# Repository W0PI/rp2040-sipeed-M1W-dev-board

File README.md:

# rp2040-sipeed-M1W-dev-board

*the names of the PCB files are different cause at the very start i sightly chnaged what i was doing and didnt know how to change kicad project names*

a rp2040 and a sippeed M1W on one board both connected by uart the M1W has a camera and lcd connector aswell as 8 mics in a circle for directional detection

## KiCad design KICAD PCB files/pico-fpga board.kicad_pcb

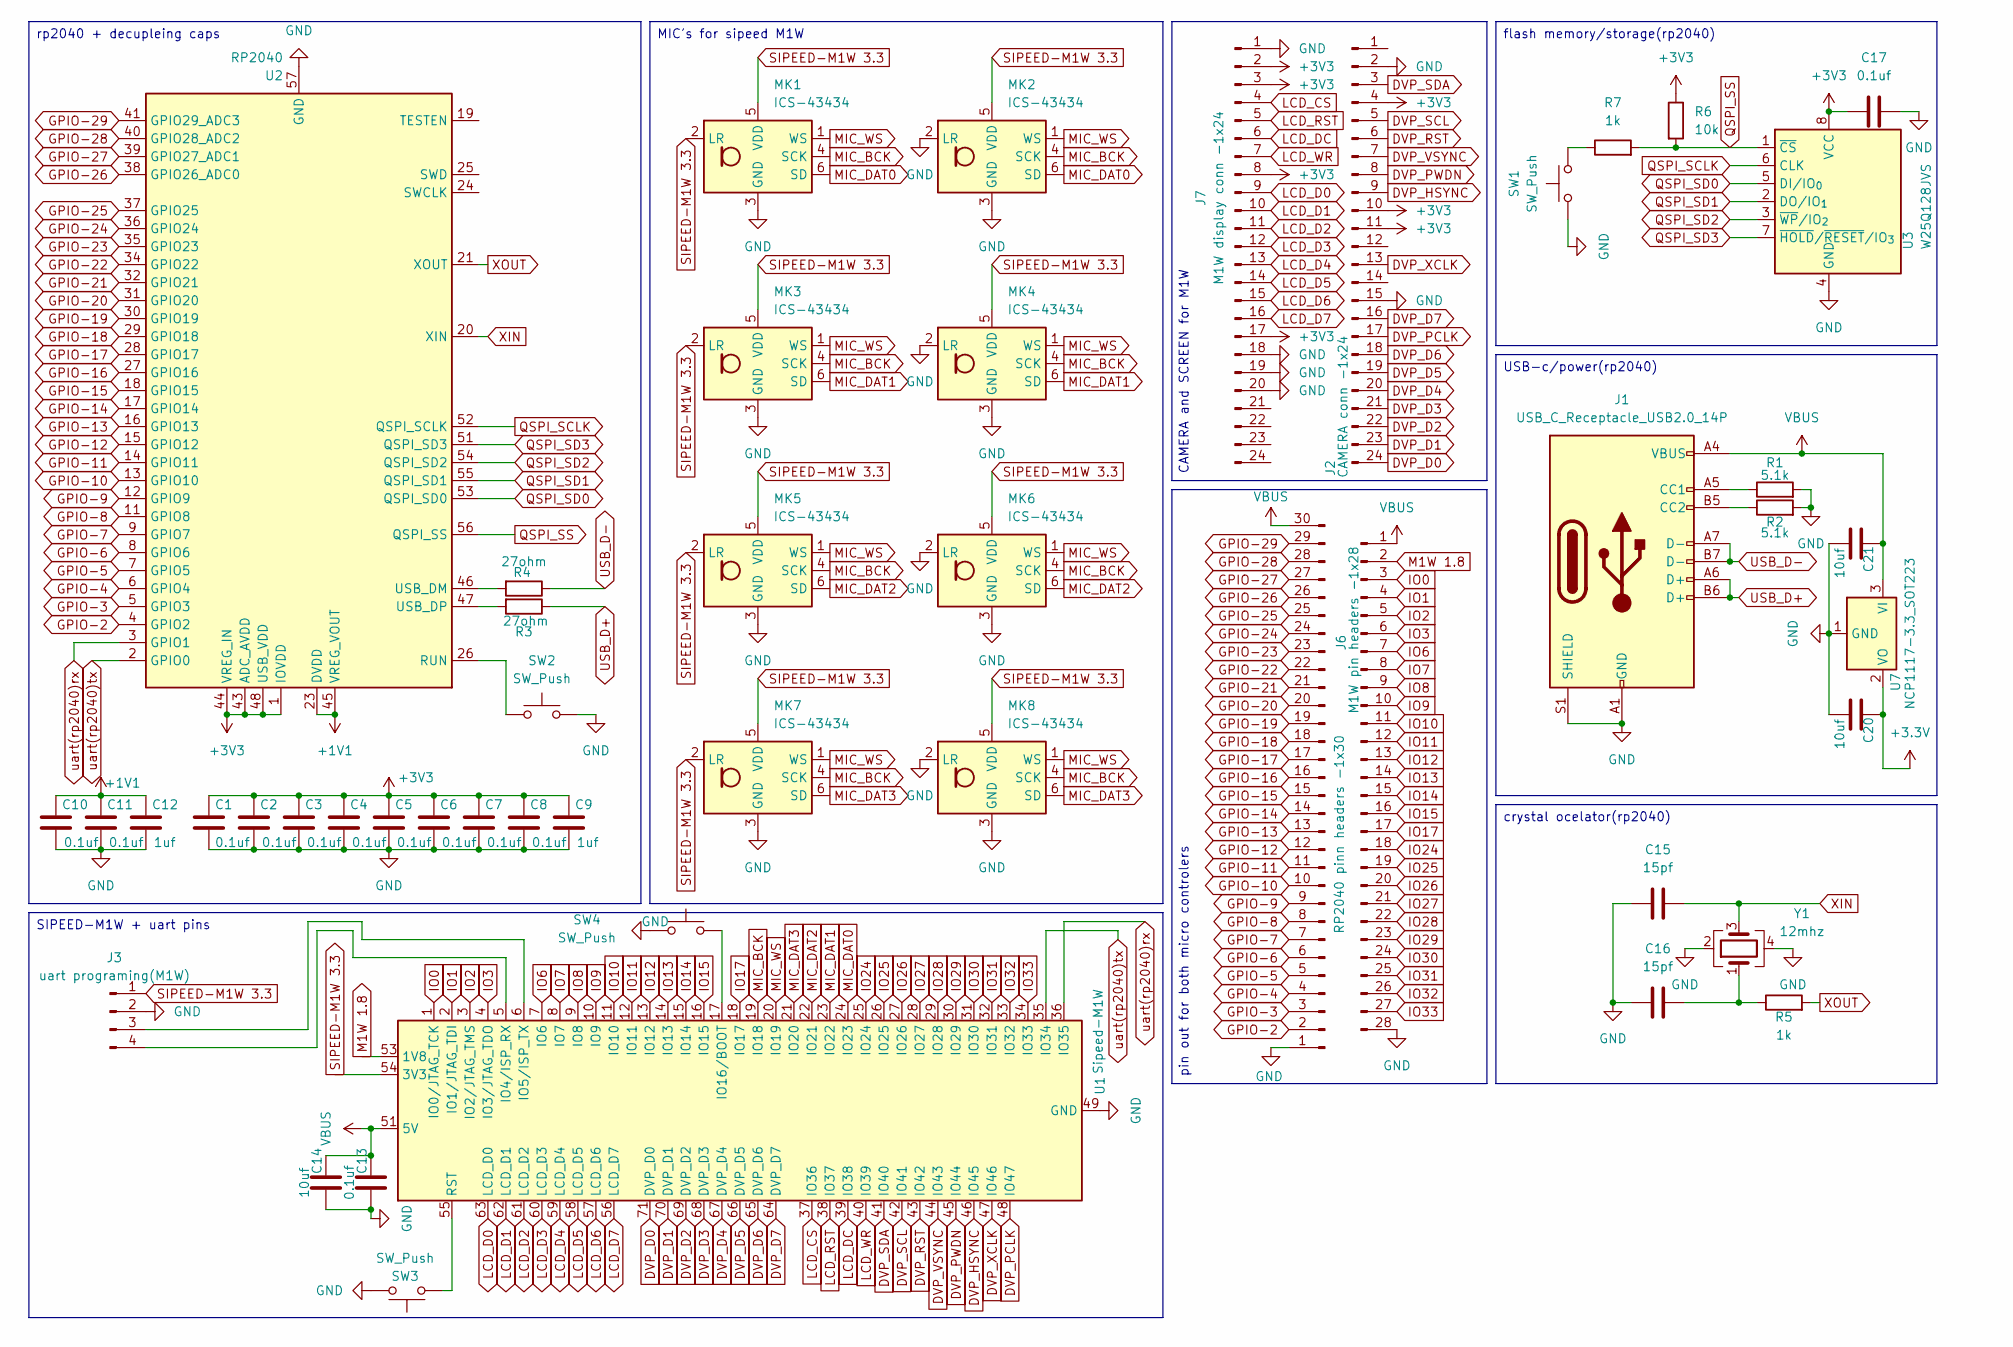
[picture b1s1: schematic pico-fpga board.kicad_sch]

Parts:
C1, C2, C3, C4, C5, C6, C7, C8, C10, C11, C13, C17: 0.1uf; 0805
C9, C12: 1uf; 0805
C14, C20, C21: 10uf; 0805
C15, C16: 15pf; 0805
J1: USB_C_Receptacle_USB2.0_14P; USB-C
J2: CAMERA conn -1x24; CAMERA conn
J3: uart programing(M1W); PinHeader_1x04_P2.54mm_Horizontal
J4: RP2040 pinn headers -1x30; PinHeader_1x30_P2.54mm_Vertical
J6: M1W pin headers -1x28; PinHeader_1x28_P2.54mm_Vertical
J7: M1W display conn -1x24; CAMERA conn
MK1, MK2, MK3, MK4, MK5, MK6, MK7, MK8: ICS-43434; InvenSense_ICS-43434-6_3.5x2.65mm
R1, R2: 5.1k; 0805
R3, R4: 27ohm; 0805
R5, R7: 1k; 0805
R6: 10k; 0805
SW1, SW2, SW3, SW4: SW_Push; button
U1: Sipeed-M1W
U2: RP2040; QFN-56-1EP_7x7mm_P0.4mm_EP3.2x3.2mm
U3: W25Q128JVS; SOIC-8_5.3x5.3mm_P1.27mm
U7: NCP1117-3.3_SOT223; SOT-223-3_TabPin2
Y1: 12mhz; 12mhz crystal

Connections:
+1V1: C10.1, C11.1, C12.1, U2.23 (DVDD), U2.45 (VREG_VOUT), U2.50 (DVDD)
+3.3V: C20.1, U7.2 (VO)
+3V3: C1.1, C2.1, C3.1, C4.1, C5.1, C6.1, C7.1, C8.1, C9.1, C17.1, J2.4, J2.10, J2.11, J7.2, J7.3, J7.8, J7.17, R6.1, U2.1 (IOVDD), U2.10 (IOVDD), U2.22 (IOVDD), U2.33 (IOVDD), U2.42 (IOVDD), U2.43 (ADC_AVDD), U2.44 (VREG_IN), U2.48 (USB_VDD), U2.49 (IOVDD), U3.8 (VCC)
DVP_D0: J2.24, U1.71 (DVP_D0)
DVP_D1: J2.23, U1.70 (DVP_D1)
DVP_D2: J2.22, U1.69 (DVP_D2)
DVP_D3: J2.21, U1.68 (DVP_D3)
DVP_D4: J2.20, U1.67 (DVP_D4)
DVP_D5: J2.19, U1.66 (DVP_D5)
DVP_D6: J2.18, U1.65 (DVP_D6)
DVP_D7: J2.16, U1.64 (DVP_D7)
DVP_HSYNC: J2.9, U1.46 (IO45)
DVP_PCLK: J2.17, U1.48 (IO47)
DVP_PWDN: J2.8, U1.45 (IO44)
DVP_RST: J2.6, U1.43 (IO42)
DVP_SCL: J2.5, U1.42 (IO41)
DVP_SDA: J2.3, U1.41 (IO40)
DVP_VSYNC: J2.7, U1.44 (IO43)
DVP_XCLK: J2.13, U1.47 (IO46)
GND: C1.2, C2.2, C3.2, C4.2, C5.2, C6.2, C7.2, C8.2, C9.2, C10.2, C11.2, C12.2, C13.1, C14.1, C15.1, C16.1, C17.2, C20.2, C21.2, J1.A1 (GND), J1.A12 (GND), J1.B1 (GND), J1.B12 (GND), J1.S1 (SHIELD), J2.2, J2.15, J3.2, J4.1, J6.28, J7.1, J7.18, J7.19, J7.20, MK1.3 (GND), MK2.2 (LR), MK2.3 (GND), MK3.3 (GND), MK4.2 (LR), MK4.3 (GND), MK5.3 (GND), MK6.2 (LR), MK6.3 (GND), MK7.3 (GND), MK8.2 (LR), MK8.3 (GND), R1.2, R2.2, SW1.1, SW2.2, SW3.2, SW4.1, U1.49 (GND), U1.50 (GND), U1.72 (GND), U2.57 (GND), U3.4 (GND), U7.1 (GND), Y1.2, Y1.4
GPIO-2: J4.2, U2.4 (GPIO2)
GPIO-3: J4.3, U2.5 (GPIO3)
GPIO-4: J4.4, U2.6 (GPIO4)
GPIO-5: J4.5, U2.7 (GPIO5)
GPIO-6: J4.6, U2.8 (GPIO6)
GPIO-7: J4.7, U2.9 (GPIO7)
GPIO-8: J4.8, U2.11 (GPIO8)
GPIO-9: J4.9, U2.12 (GPIO9)
GPIO-10: J4.10, U2.13 (GPIO10)
GPIO-11: J4.11, U2.14 (GPIO11)
GPIO-12: J4.12, U2.15 (GPIO12)
GPIO-13: J4.13, U2.16 (GPIO13)
GPIO-14: J4.14, U2.17 (GPIO14)
GPIO-15: J4.15, U2.18 (GPIO15)
GPIO-16: J4.16, U2.27 (GPIO16)
GPIO-17: J4.17, U2.28 (GPIO17)
GPIO-18: J4.18, U2.29 (GPIO18)
GPIO-19: J4.19, U2.30 (GPIO19)
GPIO-20: J4.20, U2.31 (GPIO20)
GPIO-21: J4.21, U2.32 (GPIO21)
GPIO-22: J4.22, U2.34 (GPIO22)
GPIO-23: J4.23, U2.35 (GPIO23)
GPIO-24: J4.24, U2.36 (GPIO24)
GPIO-25: J4.25, U2.37 (GPIO25)
GPIO-26: J4.26, U2.38 (GPIO26_ADC0)
GPIO-27: J4.27, U2.39 (GPIO27_ADC1)
GPIO-28: J4.28, U2.40 (GPIO28_ADC2)
GPIO-29: J4.29, U2.41 (GPIO29_ADC3)
IO0: J6.3, U1.1 (IO0/JTAG_TCK)
IO1: J6.4, U1.2 (IO1/JTAG_TDI)
IO2: J6.5, U1.3 (IO2/JTAG_TMS)
IO3: J6.6, U1.4 (IO3/JTAG_TDO)
IO6: J6.7, U1.7 (IO6)
IO7: J6.8, U1.8 (IO7)
IO8: J6.9, U1.9 (IO8)
IO9: J6.10, U1.10 (IO9)
IO10: J6.11, U1.11 (IO10)
IO11: J6.12, U1.12 (IO11)
IO12: J6.13, U1.13 (IO12)
IO13: J6.14, U1.14 (IO13)
IO14: J6.15, U1.15 (IO14)
IO15: J6.16, U1.16 (IO15)
IO17: J6.17, U1.18 (IO17)
IO24: J6.18, U1.25 (IO24)
IO25: J6.19, U1.26 (IO25)
IO26: J6.20, U1.27 (IO26)
IO27: J6.21, U1.28 (IO27)
IO28: J6.22, U1.29 (IO28)
IO29: J6.23, U1.30 (IO29)
IO30: J6.24, U1.31 (IO30)
IO31: J6.25, U1.32 (IO31)
IO32: J6.26, U1.33 (IO32)
IO33: J6.27, U1.34 (IO33)
LCD_CS: J7.4, U1.37 (IO36)
LCD_D0: J7.9, U1.63 (LCD_D0)
LCD_D1: J7.10, U1.62 (LCD_D1)
LCD_D2: J7.11, U1.61 (LCD_D2)
LCD_D3: J7.12, U1.60 (LCD_D3)
LCD_D4: J7.13, U1.59 (LCD_D4)
LCD_D5: J7.14, U1.58 (LCD_D5)
LCD_D6: J7.15, U1.57 (LCD_D6)
LCD_D7: J7.16, U1.56 (LCD_D7)
LCD_DC: J7.6, U1.39 (IO38)
LCD_RST: J7.5, U1.38 (IO37)
LCD_WR: J7.7, U1.40 (IO39)
M1W 1.8: J6.2, U1.53 (1V8)
MIC_BCK: MK1.4 (SCK), MK2.4 (SCK), MK3.4 (SCK), MK4.4 (SCK), MK5.4 (SCK), MK6.4 (SCK), MK7.4 (SCK), MK8.4 (SCK), U1.19 (IO18)
MIC_DAT0: MK1.6 (SD), MK2.6 (SD), U1.24 (IO23)
MIC_DAT1: MK3.6 (SD), MK4.6 (SD), U1.23 (IO22)
MIC_DAT2: MK5.6 (SD), MK6.6 (SD), U1.22 (IO21)
MIC_DAT3: MK7.6 (SD), MK8.6 (SD), U1.21 (IO20)
MIC_WS: MK1.1 (WS), MK2.1 (WS), MK3.1 (WS), MK4.1 (WS), MK5.1 (WS), MK6.1 (WS), MK7.1 (WS), MK8.1 (WS), U1.20 (IO19)
unnamed: C16.2, R5.1, Y1.1
unnamed: J1.A5 (CC1), R1.1
unnamed: J1.B5 (CC2), R2.1
unnamed: J3.3, U1.6 (IO5/ISP_TX)
unnamed: J3.4, U1.5 (IO4/ISP_RX)
unnamed: R7.1, SW1.2
unnamed: SW4.2, U1.17 (IO16/BOOT)
unnamed: SW3.1, U1.55 (RST)
unnamed: SW2.1, U2.26 (RUN)
unnamed: R4.2, U2.46 (USB_DM)
unnamed: R3.2, U2.47 (USB_DP)
QSPI_SCLK: U2.52 (QSPI_SCLK), U3.6 (CLK)
QSPI_SD0: U2.53 (QSPI_SD0), U3.5 (DI/IO_{0})
QSPI_SD1: U2.55 (QSPI_SD1), U3.2 (DO/IO_{1})
QSPI_SD2: U2.54 (QSPI_SD2), U3.3 (~WP/IO_{2})
QSPI_SD3: U2.51 (QSPI_SD3), U3.7 (~HOLD/~RESET/IO_{3})
QSPI_SS: R6.2, R7.2, U2.56 (QSPI_SS), U3.1 (~CS)
SIPEED-M1W 3.3: J3.1, MK1.2 (LR), MK1.5 (VDD), MK2.5 (VDD), MK3.2 (LR), MK3.5 (VDD), MK4.5 (VDD), MK5.2 (LR), MK5.5 (VDD), MK6.5 (VDD), MK7.2 (LR), MK7.5 (VDD), MK8.5 (VDD), U1.54 (3V3)
USB_D+: J1.A6 (D+), J1.B6 (D+), R3.1
USB_D-: J1.A7 (D-), J1.B7 (D-), R4.1
VBUS: C13.2, C14.2, C21.1, J1.A4 (VBUS), J1.A9 (VBUS), J1.B4 (VBUS), J1.B9 (VBUS), J4.30, J6.1, U1.51 (5V), U1.52 (5V), U7.3 (VI)
XIN: C15.2, U2.20 (XIN), Y1.3
XOUT: R5.2, U2.21 (XOUT)
uart(rp2040)rx: U1.36 (IO35), U2.3 (GPIO1)
uart(rp2040)tx: U1.35 (IO34), U2.2 (GPIO0)

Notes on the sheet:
MIC's for sipeed M1W
flash memory/storage(rp2040)
pin out for both micro controlers
SIPEED-M1W + uart pins
crystal ocelator(rp2040)
rp2040 + decupleing caps
CAMERA and SCREEN for M1W
USB-c/power(rp2040)

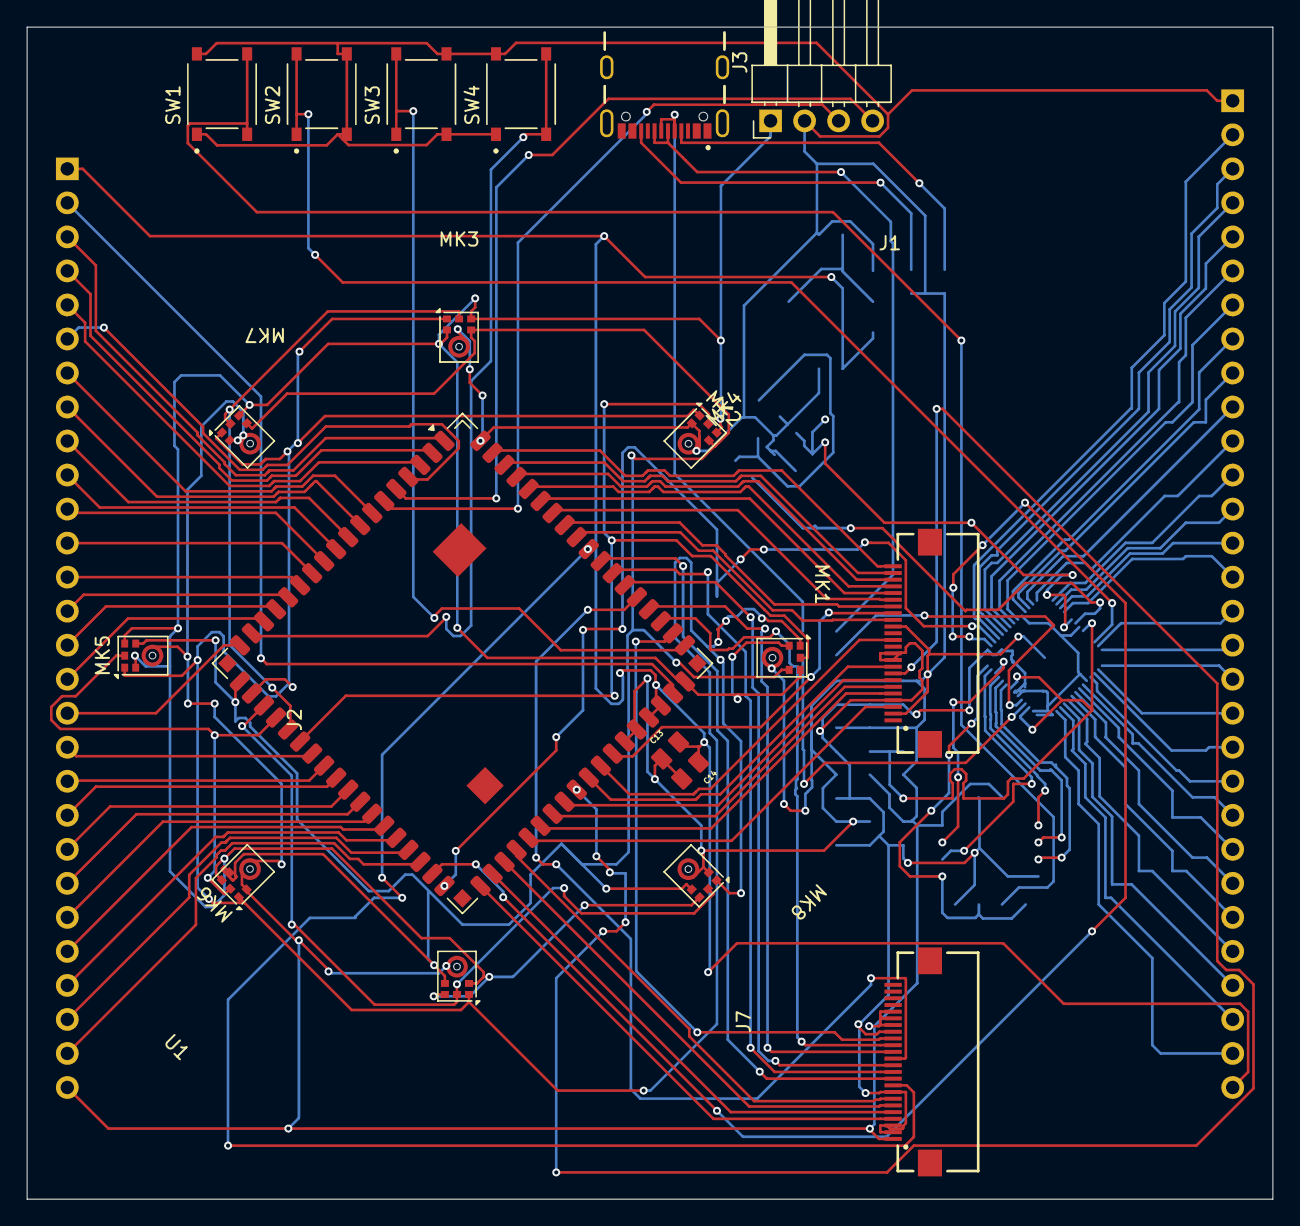
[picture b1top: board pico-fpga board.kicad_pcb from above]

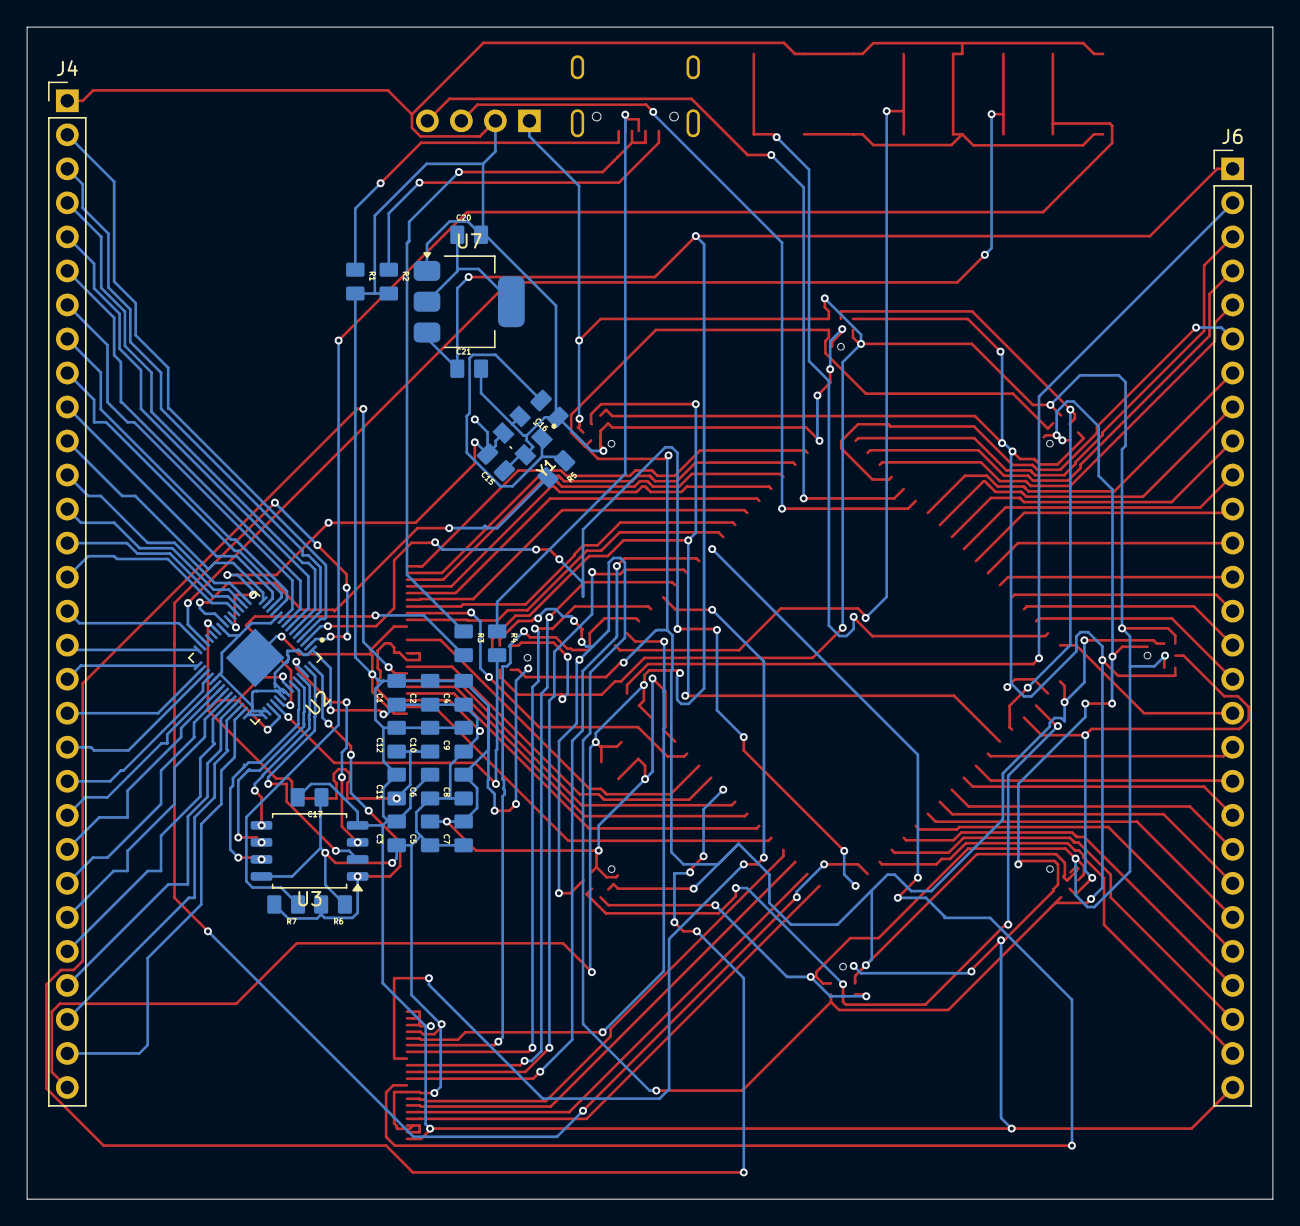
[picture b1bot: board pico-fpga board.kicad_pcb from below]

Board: 2 copper layers, 93.0 x 87.5 mm, 49 parts (30 on the bottom side), 117 nets.

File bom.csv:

Designator,Footprint,Quantity,Value,LCSC Part #
"C1, C10, C11, C13, C17, C2, C3, C4, C5, C6, C7, C8",0805,12,0.1uf,
"C12, C9",0805,2,1uf,
"C14, C20, C21",0805,3,10uf,
"C15, C16",0805,2,15pf,
J1,USB-C,1,USB_C_Receptacle_USB2.0_14P,
J2,CAMERA conn,1,CAMERA conn -1x24,
J3,PinHeader_1x04_P2.54mm_Horizontal,1,uart programing(M1W),
J4,PinHeader_1x30_P2.54mm_Vertical,1,RP2040 pinn headers -1x30,
J6,PinHeader_1x28_P2.54mm_Vertical,1,M1W pin headers -1x28,
J7,CAMERA conn,1,M1W display conn -1x24,
"MK1, MK2, MK3, MK4, MK5, MK6, MK7, MK8",InvenSense_ICS-43434-6_3.5x2.65mm,8,ICS-43434,
"R1, R2",0805,2,5.1k,
"R3, R4",0805,2,27ohm,
"R5, R7",0805,2,1k,
R6,0805,1,10k,
"SW1, SW2, SW3, SW4",button,4,SW_Push,
U1,Sipeed-M1W,1,Sipeed-M1W,
U2,RP2040,1,RP2040,
U3,SOIC-8_5.3x5.3mm_P1.27mm,1,W25Q128JVS,
U7,SOT-223-3_TabPin2,1,NCP1117-3.3_SOT223,
Y1,12mhz crystal,1,12mhz,

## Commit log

2025-12-31 Initial commit of RP2040 Sipeed M1W dev board project
